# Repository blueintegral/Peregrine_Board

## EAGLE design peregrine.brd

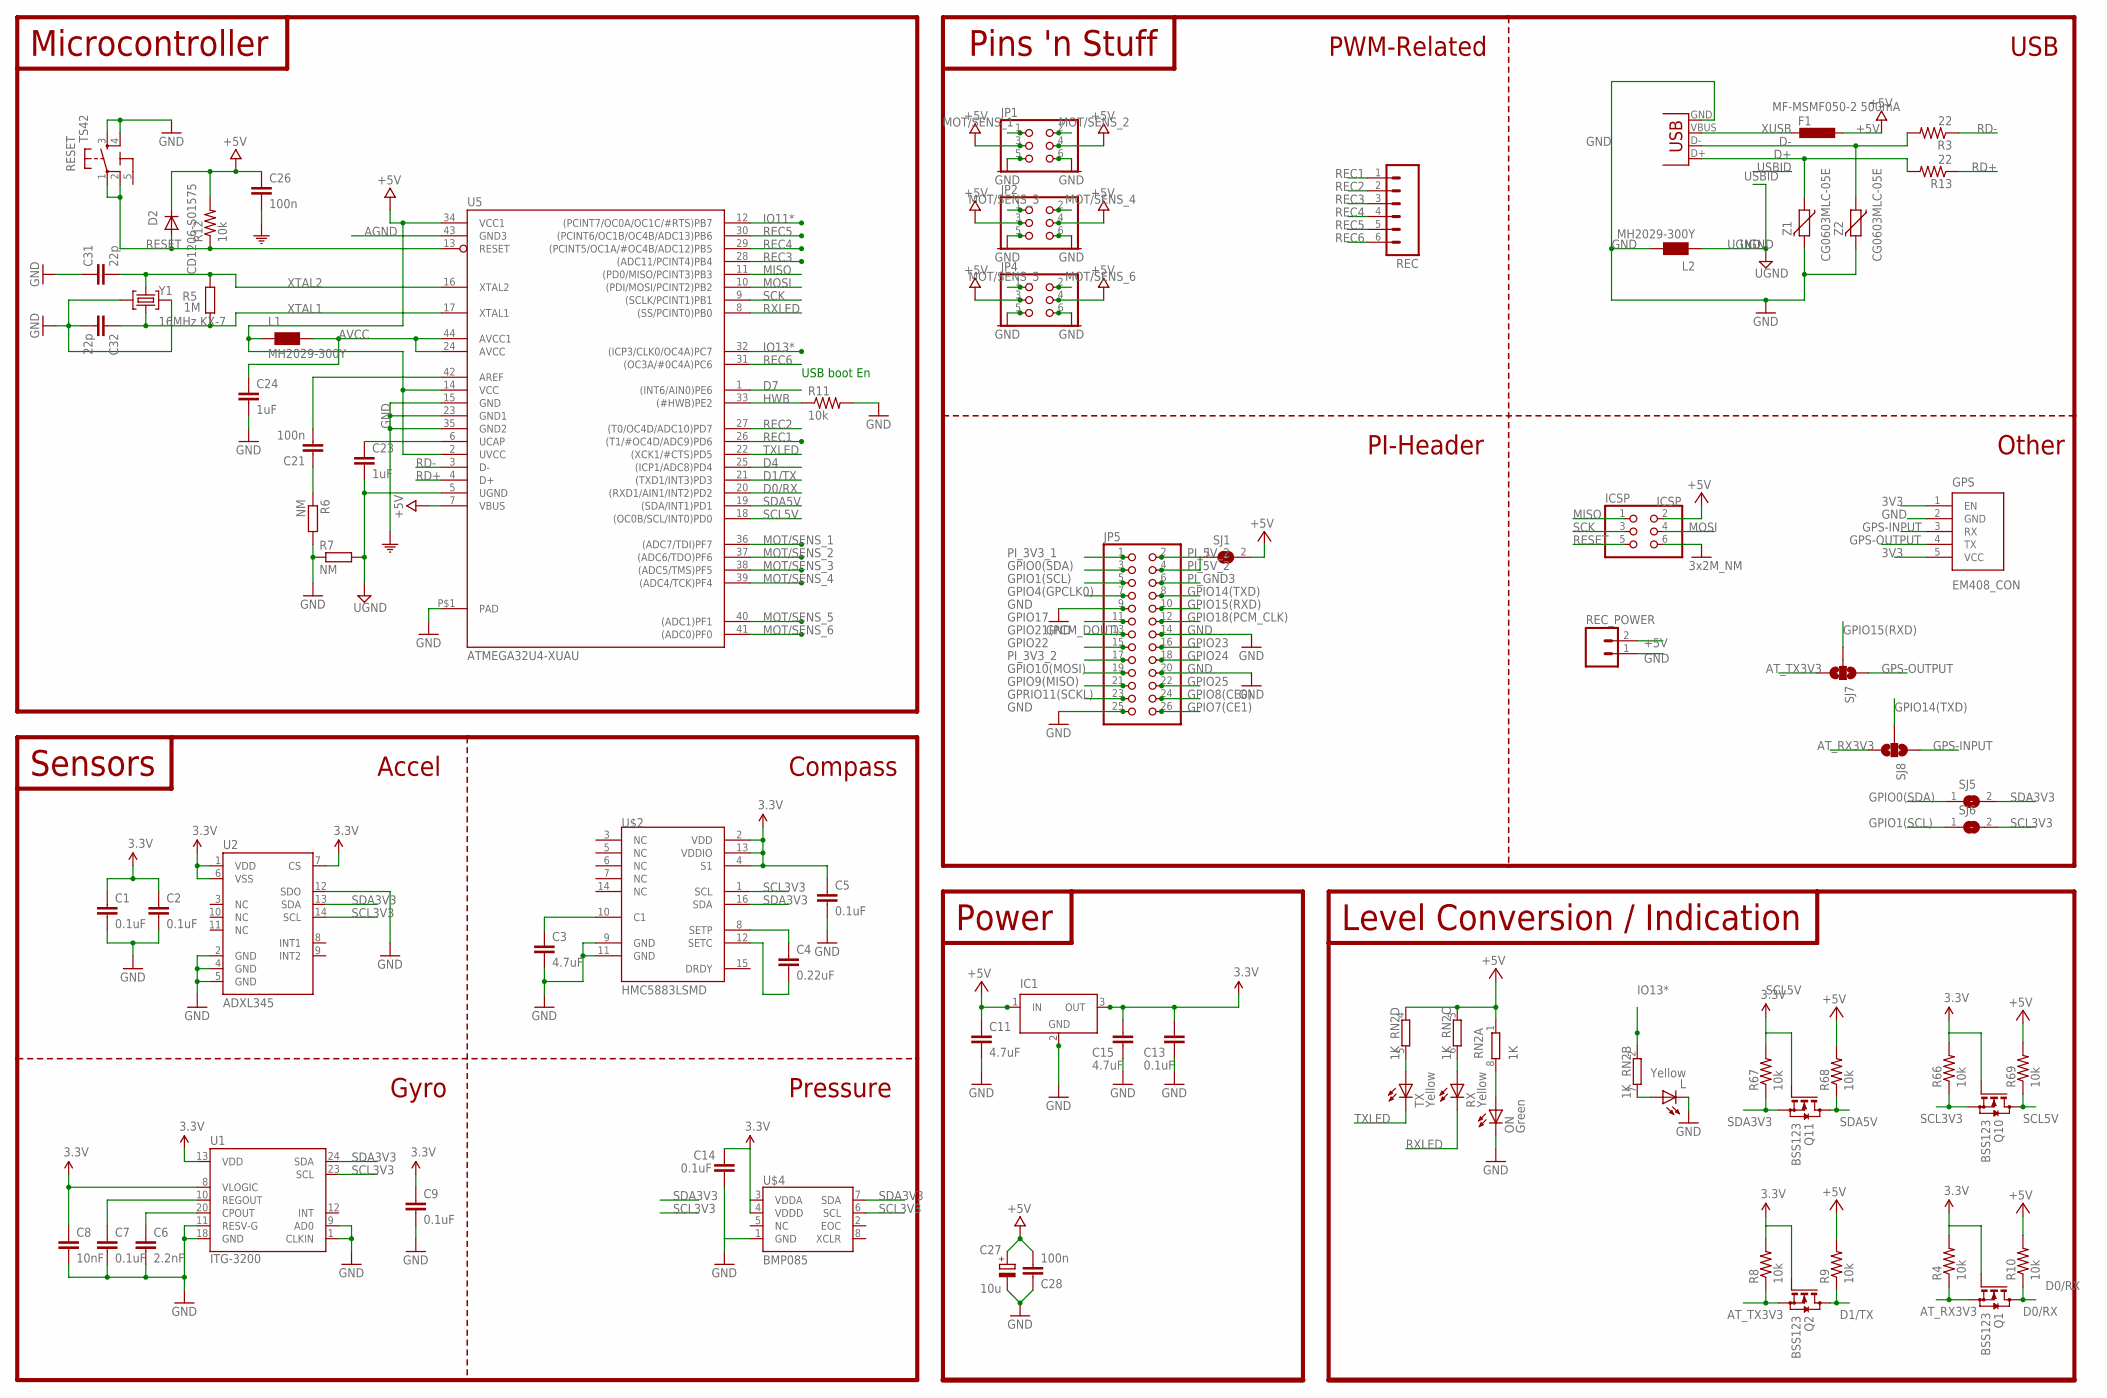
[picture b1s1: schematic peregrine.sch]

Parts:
C1, C2, C5, C7, C9, C13, C14: 0.1uF; 0402-CAP
C3, C11, C15: 4.7uF; 0402-CAP
C4: 0.22uF; 0402-CAP
C6: 2.2nF; 0402-CAP
C8: 10nF; 0402-CAP
C21, C26, C28: 100n; C0603-ROUND
C23, C24: 1uF; C0603-ROUND
C27: 10u; SMC_B
C31, C32: 22p; C0603-ROUND
D2: CD1206-S01575; MINIMELF
F1: MF-MSMF050-2 500mA; L1812
GPS: EM408_CON
IC1: LT1129CST5; SOT223
ICSP: ICSP; 2X03
JP1, JP2, JP4: PINHD-2X3; 2X03
JP5: PINHD-2X13; 2X13
L: Yellow; CHIPLED_0805
L1, L2: MH2029-300Y; 0805
ON: Green; CHIPLED_0805
Q1, Q2, Q10, Q11: BSS123; SOT23
R3, R13: 22; 0603-RES
R4, R8, R9, R10, R66, R67, R68, R69: 10k; 0603-RES
R5: 1M; R0603-ROUND
R6, R7: NM; R0603-ROUND
R11, R12: 10k; R0603
REC: M06SIP; 1X06
REC_POWER: M02PTH; 1X02
RESET: TS42
RN2: 1K; CAY16
RX: Yellow; CHIPLED_0805
SJ1, SJ5, SJ6: SJ
SJ7, SJ8: SOLDERJUMPER_2WAYS; SJ_3
TX: Yellow; CHIPLED_0805
U1: ITG-3200; QFN-24
U2: ADXL345; LGA14
U5: ATMEGA32U4-XUAU; TQFP44-PAD
U$2: HMC5883LSMD; 16LPCC
U$4: BMP085
X2: USB-MICROB
Y1: 16MHz KX-7; CRYSTAL-3.2-2.5
Z1, Z2: CG0603MLC-05E; CT/CN0603

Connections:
3V3: C1.1, C2.1, C5.1, C8.1, C9.1, C13.1, C14.1, C15.1, GPS.1 (EN), GPS.5 (VCC), IC1.3 (OUT), Q1.1 (G), Q2.1 (G), Q10.1 (G), Q11.1 (G), R4.2, R8.2, R66.2, R67.2, U1.8 (VLOGIC), U1.13 (VDD), U2.1 (VDD), U2.6 (VSS), U2.7 (CS), U$2.2 (VDD), U$2.4 (S1), U$2.13 (VDDIO), U$4.3 (VDDA), U$4.4 (VDDD)
5-GND: RESET.5 (5-GND)
+5V: C11.1, C26.1, C27.+, C28.2, D2.C, F1.1, IC1.1 (IN), ICSP.2, JP1.3, JP1.4, JP2.3, JP2.4, JP4.3, JP4.4, L1.1, R9.2, R10.2, R12.2, R68.2, R69.2, REC_POWER.2, RN2.1, RN2.3 (1), RN2.4 (1), SJ1.2, U5.2 (UVCC), U5.7 (VBUS), U5.14 (VCC), U5.34 (VCC1)
AGND: C21.1, R6.1, U5.43 (GND3)
AREF: C21.2, U5.42 (AREF)
AT_RX3V3: Q1.2 (S), R4.1, SJ8.3
AT_TX3V3: Q2.2 (S), R8.1, SJ7.3
AVCC: C24.1, L1.2, U5.24 (AVCC), U5.44 (AVCC1)
D0/RX: Q1.3 (D), R10.1, U5.20 ((RXD1/AIN1/INT2)PD2)
D1/TX: Q2.3 (D), R9.1, U5.21 ((TXD1/INT3)PD3)
D4: U5.25 ((ICP1/ADC8)PD4)
D7: U5.1 ((INT6/AIN0)PE6)
D+: R13.2, X2.D+, Z1.1
D-: R3.2, X2.D-, Z2.1
GND: C1.2, C2.2, C3.2, C5.2, C6.2, C7.2, C8.2, C9.2, C11.2, C13.2, C14.2, C15.2, C24.2, C26.2, C27.-, C28.1, C31.1, C32.2, GPS.2 (GND), IC1.2 (GND), IC1.4 (GND), ICSP.6, JP1.5, JP1.6, JP2.5, JP2.6, JP4.5, JP4.6, JP5.9, JP5.14, JP5.20, JP5.25, L.C, L2.2, ON.C, R6.2, R7.1, R11.2, REC_POWER.1, RESET.3, RESET.4, U1.1 (CLKIN), U1.9 (AD0), U1.11 (RESV-G), U1.18 (GND), U2.2 (GND), U2.4 (GND), U2.5 (GND), U2.12 (SDO), U5.15 (GND), U5.23 (GND1), U5.35 (GND2), U5.P$1 (PAD), U$2.9 (GND), U$2.11 (GND), U$4.1 (GND), X2.GND, Y1.2 (GND), Y1.4 (GND), Z1.2, Z2.2
GPIO0(SDA): JP5.3, SJ5.1
GPIO1(SCL): JP5.5, SJ6.1
GPIO4(GPCLK0): JP5.7
GPIO7(CE1): JP5.26
GPIO8(CE0): JP5.24
GPIO9(MISO): JP5.21
GPIO10(MOSI): JP5.19
GPIO14(TXD): JP5.8, SJ8.2
GPIO15(RXD): JP5.10, SJ7.2
GPIO17: JP5.11
GPIO18(PCM_CLK): JP5.12
GPIO21(PCM_DOUT): JP5.13
GPIO22: JP5.15
GPIO23: JP5.16
GPIO24: JP5.18
GPIO25: JP5.22
GPRIO11(SCKL): JP5.23
GPS-INPUT: GPS.3 (RX), SJ8.1
GPS-OUTPUT: GPS.4 (TX), SJ7.1
HWB: R11.1, U5.33 ((#HWB)PE2)
IO11*: U5.12 ((PCINT7/OC0A/OC1C/#RTS)PB7)
IO13*: RN2.2 (1), U5.32 ((ICP3/CLK0/OC4A)PC7)
MISO: ICSP.1, U5.11 ((PD0/MISO/PCINT3)PB3)
MOSI: ICSP.4, U5.10 ((PDI/MOSI/PCINT2)PB2)
MOT/SENS_1: JP1.1, U5.36 ((ADC7/TDI)PF7)
MOT/SENS_2: JP1.2, U5.37 ((ADC6/TDO)PF6)
MOT/SENS_3: JP2.1, U5.38 ((ADC5/TMS)PF5)
MOT/SENS_4: JP2.2, U5.39 ((ADC4/TCK)PF4)
MOT/SENS_5: JP4.1, U5.40 ((ADC1)PF1)
MOT/SENS_6: JP4.2, U5.41 ((ADC0)PF0)
unnamed: C3.1, U$2.10 (C1)
unnamed: C4.1, U$2.8 (SETP)
unnamed: C4.2, U$2.12 (SETC)
unnamed: RN2.5 (2), TX.A
unnamed: C6.1, U1.20 (CPOUT)
unnamed: C7.1, U1.10 (REGOUT)
unnamed: ON.A, RN2.8 (2)
unnamed: L.A, RN2.7 (2)
unnamed: RN2.6 (2), RX.A
PI_3V3_1: JP5.1
PI_3V3_2: JP5.17
PI_5V_2: JP5.2, JP5.4, SJ1.1
PI_GND3: JP5.6
RD+: R13.1, U5.4 (D+)
RD-: R3.1, U5.3 (D-)
REC1: REC.1, U5.26 ((T1/#OC4D/ADC9)PD6)
REC2: REC.2, U5.27 ((T0/OC4D/ADC10)PD7)
REC3: REC.3, U5.28 ((ADC11/PCINT4)PB4)
REC4: REC.4, U5.29 ((PCINT5/OC1A/#OC4B/ADC12)PB5)
REC5: REC.5, U5.30 ((PCINT6/OC1B/OC4B/ADC13)PB6)
REC6: REC.6, U5.31 ((OC3A/#0C4A)PC6)
RESET: D2.A, ICSP.5, R12.1, RESET.1, RESET.2, U5.13 (RESET)
RXLED: RX.C, U5.8 ((SS/PCINT0)PB0)
SCK: ICSP.3, U5.9 ((SCLK/PCINT1)PB1)
SCL3V3: Q10.2 (S), R66.1, SJ6.2, U1.23 (SCL), U2.14 (SCL), U$2.1 (SCL), U$4.6 (SCL)
SCL5V: Q10.3 (D), R69.1, U5.18 ((OC0B/SCL/INT0)PD0)
SDA3V3: Q11.2 (S), R67.1, SJ5.2, U1.24 (SDA), U2.13 (SDA), U$2.16 (SDA), U$4.7 (SDA)
SDA5V: Q11.3 (D), R68.1, U5.19 ((SDA/INT1)PD1)
TXLED: TX.C, U5.22 ((XCK1/#CTS)PD5)
UCAP: C23.1, U5.6 (UCAP)
UGND: C23.2, L2.1, R7.2, U5.5 (UGND)
XTAL1: C32.1, R5.1, U5.17 (XTAL1), Y1.1 (C1)
XTAL2: C31.2, R5.2, U5.16 (XTAL2), Y1.3 (C2)
XUSB: F1.2, X2.VBUS

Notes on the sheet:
Sensors
Power
Pins 'n Stuff
Microcontroller
USB boot En
Level Conversion / Indication
Accel
Gyro
Compass
Pressure
PI-Header
PWM-Related
Other
USB

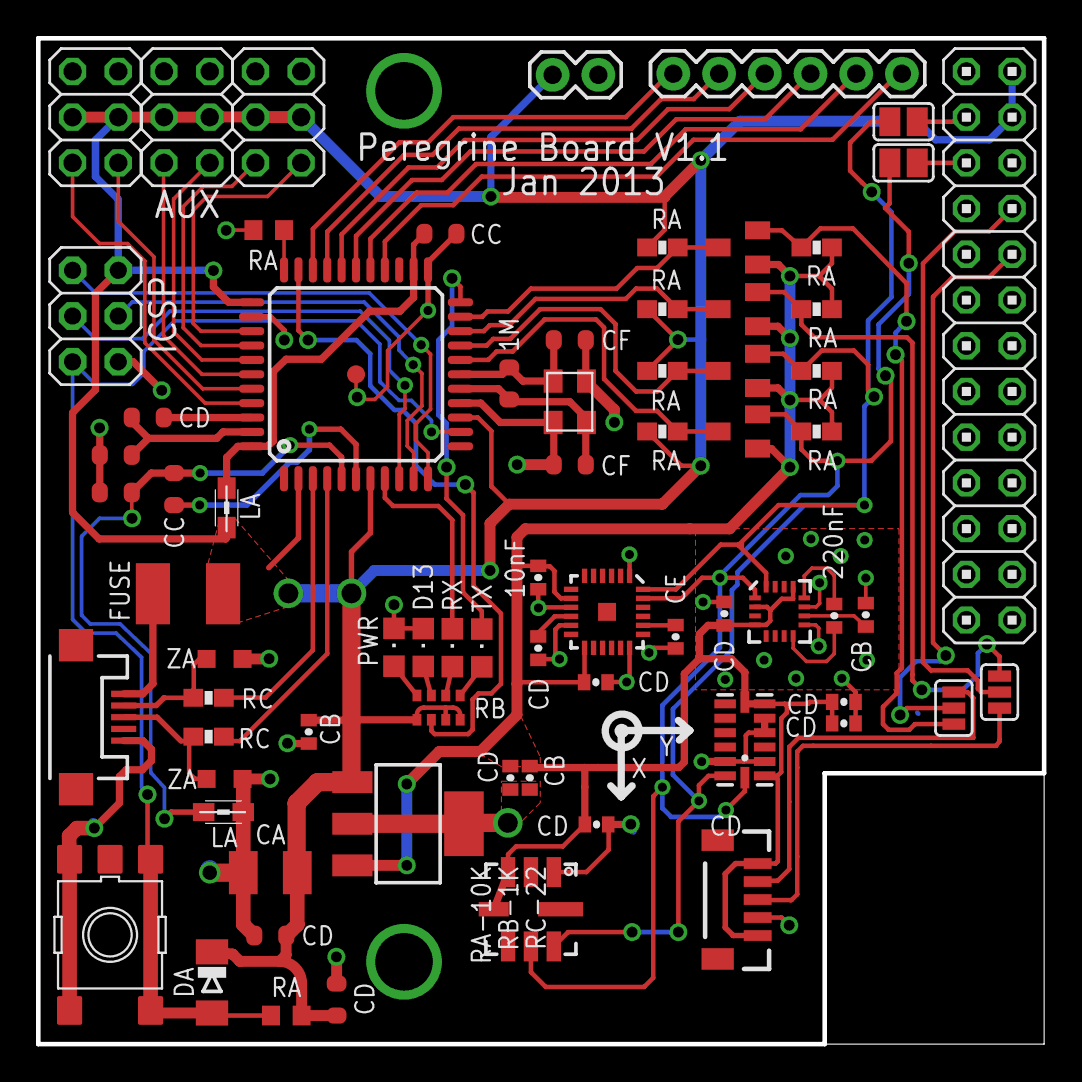
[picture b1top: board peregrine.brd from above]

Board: 2 copper layers, 55.9 x 55.9 mm, 73 parts (1 on the bottom side), 59 nets.

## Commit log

2012-09-17 Added schematic for everything except barometer
    Layout also needs to be adjusted for an R Pi.
2012-09-17 Added gitignore for eagle temp files
2012-09-28 Added schematics, TODO, fixed gitignore
2012-10-05 Re-arranged Schematic, updated uC to ATMEGA32U4
2012-10-06 Remove RazorIMU brd
2012-10-06 Added barometers, JTAG, datasheets
2012-10-13 Added outline and Pi GPIO, crappy placement
2012-10-16 Schematic Changes
    Changed a number of nets to reflect desired configuration. Added solder
    jumpers for potential "serial dyslexia" resloution. Still needs quite a
    few net changes to be completely accurate.
2012-10-24 Tweaked placement
2012-11-04 Changed around layout.
    Changed a bunch of headers so that they were small perofile or locking.
    Ignored RCA plug, just assuming that we can build above it. Added two
    standoff holes for support above the board. The standoffs would touch on
    blank spots on the pi.
2012-11-14 Initial route completed
    The other random files are from converting it to a couple different
    formats to try some autorouters out.
2012-11-15 Many changes.
    Added level conversion to schematic. Had to re-do route because of many
    added components. Also, connected a number of things which needed
    connections in schematic. Route about 80% done.
2012-11-15 routing.
2012-11-24 Fixed some stuff
2012-11-26 Fixed silk
2012-12-07 Moderate Re-Route.`
    Everything on top layer, a bit more pretty, some schematic changes, new
    silk.
2012-12-07 Fixed Compass Ground Plane
    Added some additional ground plan volume around the compass.
2012-12-14 added gerbers
2013-01-08 Not a change, Just including version of board which was sent out.
2013-01-22 Made room in layout for cutout
2013-01-25 Added notch for RCA connector
2013-01-28 Changed outline, removed unused parts, via stops
2013-01-29 Moved outline a bit, added gerbers
2013-03-05 Corrected silk labeling error
